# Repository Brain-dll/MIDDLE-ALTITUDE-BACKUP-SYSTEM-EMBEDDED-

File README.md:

# technofest-3000
This project are developed for model rocket competition of technofest. Main purpose is developing avionic systems

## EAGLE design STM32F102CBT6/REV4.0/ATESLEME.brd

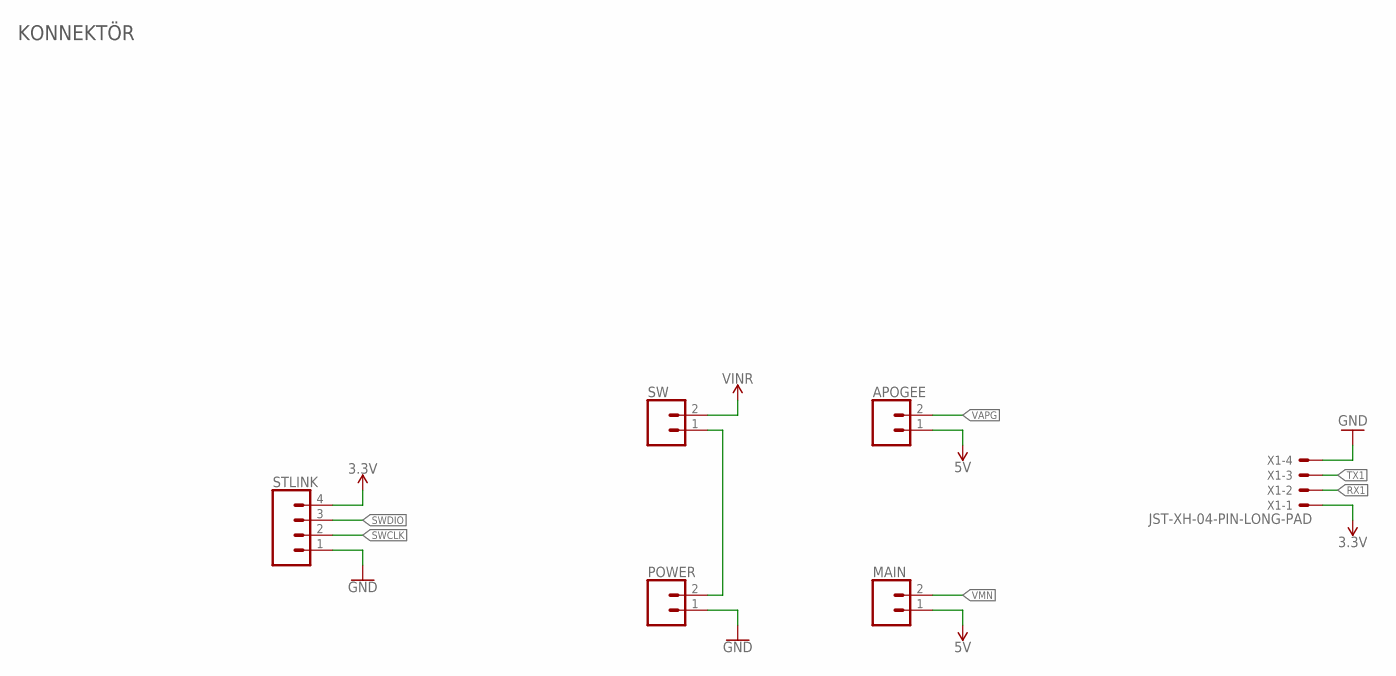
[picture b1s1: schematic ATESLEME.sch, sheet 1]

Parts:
APOGEE: CONN_023.5MM-NO_SILK; SCREWTERMINAL-3.5MM-2-NS
MAIN: CONN_023.5MM-NO_SILK; SCREWTERMINAL-3.5MM-2-NS
POWER: CONN_023.5MM-NO_SILK; SCREWTERMINAL-3.5MM-2-NS
STLINK: CONN_04; 1X04
SW: CONN_023.5MM-NO_SILK; SCREWTERMINAL-3.5MM-2-NS
X1: JST-XH-04-PIN-LONG-PAD; JST-XH-04-PACKAGE-LONG-PAD

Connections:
3.3V: STLINK.4, X1.1; also elsewhere on the board
5V: APOGEE.1, MAIN.1; also elsewhere on the board
GND: POWER.1, STLINK.1, X1.4; also elsewhere on the board
unnamed: POWER.2, SW.1
RX1: X1.2; also elsewhere on the board
SWCLK: STLINK.2; also elsewhere on the board
SWDIO: STLINK.3; also elsewhere on the board
TX1: X1.3; also elsewhere on the board
VAPG: APOGEE.2; also elsewhere on the board
VIN: SW.2; also elsewhere on the board
VMN: MAIN.2; also elsewhere on the board

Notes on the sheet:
KONNEKTÖR

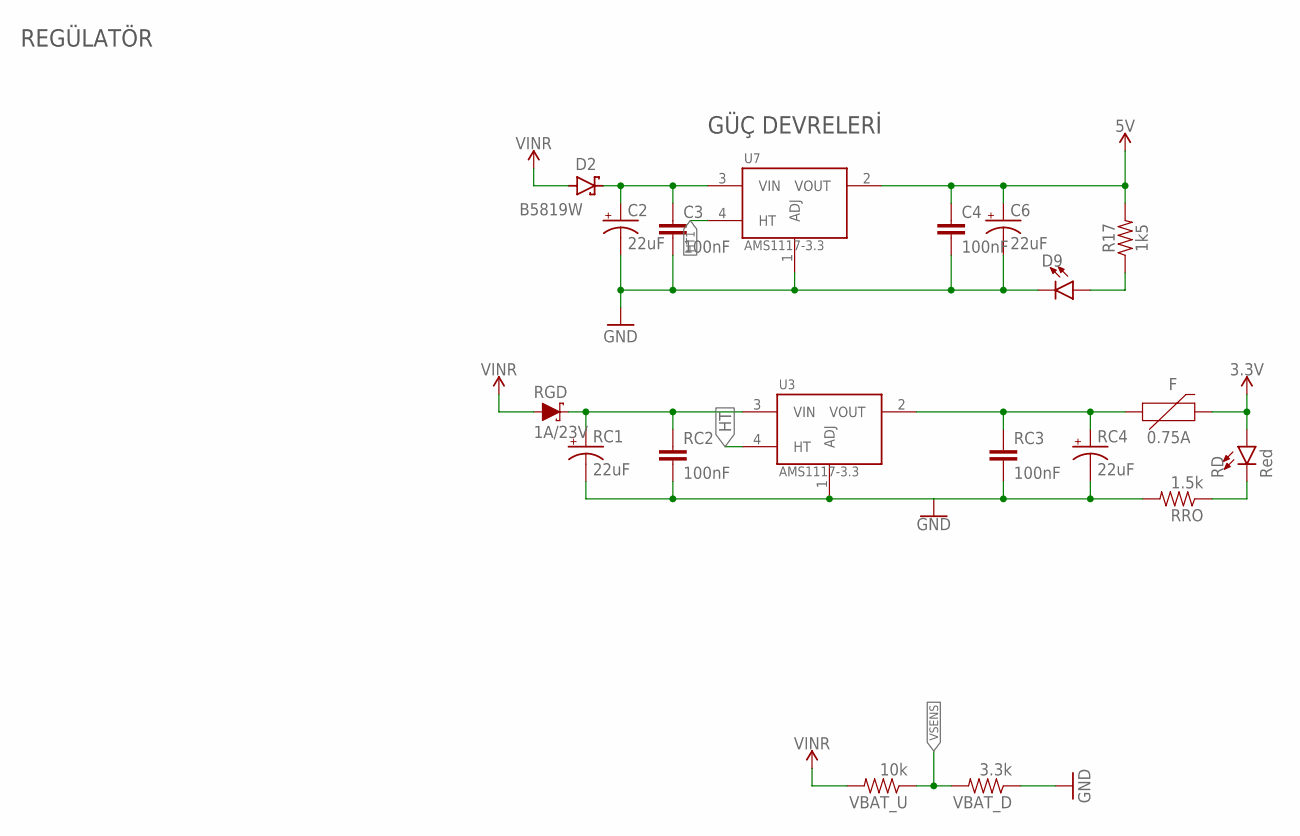
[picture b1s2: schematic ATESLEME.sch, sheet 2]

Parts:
C2, C6: 22uF; EIA3528
C3, C4: 100nF; 0603
D2: B5819W; SODFL3718X115
D9: LED0603; LED-0603
F: 0.75A; 1206
R17: 1k5; 0603
RC1, RC4: 22uF; EIA3528
RC2, RC3: 100nF; 0603
RD: Red; LED-0603
RGD: 1A/23V; SOD-323
RRO: 1.5k; 0603-RES
U3, U7: AMS1117-3.3; SOT229P700X180-4N
VBAT_D: 3.3k; 0603-RES
VBAT_U: 10k; 0603-RES

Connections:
3.3V: F.2, RD.A; also elsewhere on the board
5V: C4.1, C6.A (+), R17.2, U7.2 (VOUT); also elsewhere on the board
GND: C2.C (-), C3.2, C4.2, C6.C (-), D9.C, RC1.C (-), RC2.2, RC3.2, RC4.C (-), RRO.2, U3.1 (ADJ), U7.1 (ADJ), VBAT_D.1; also elsewhere on the board
HT: U3.4 (HT)
HT1: U7.4 (HT)
unnamed: F.1, RC3.1, RC4.A (+), U3.2 (VOUT)
unnamed: RD.C, RRO.1
unnamed: C2.A (+), C3.1, D2.1 (C), U7.3 (VIN)
unnamed: D9.A, R17.1
VIN: D2.2 (A), RGD.A, VBAT_U.2; also elsewhere on the board
VNR: RC1.A (+), RC2.1, RGD.C, U3.3 (VIN)
VSENS: VBAT_D.2, VBAT_U.1; also elsewhere on the board

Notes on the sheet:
REGÜLATÖR
GÜÇ DEVRELERİ

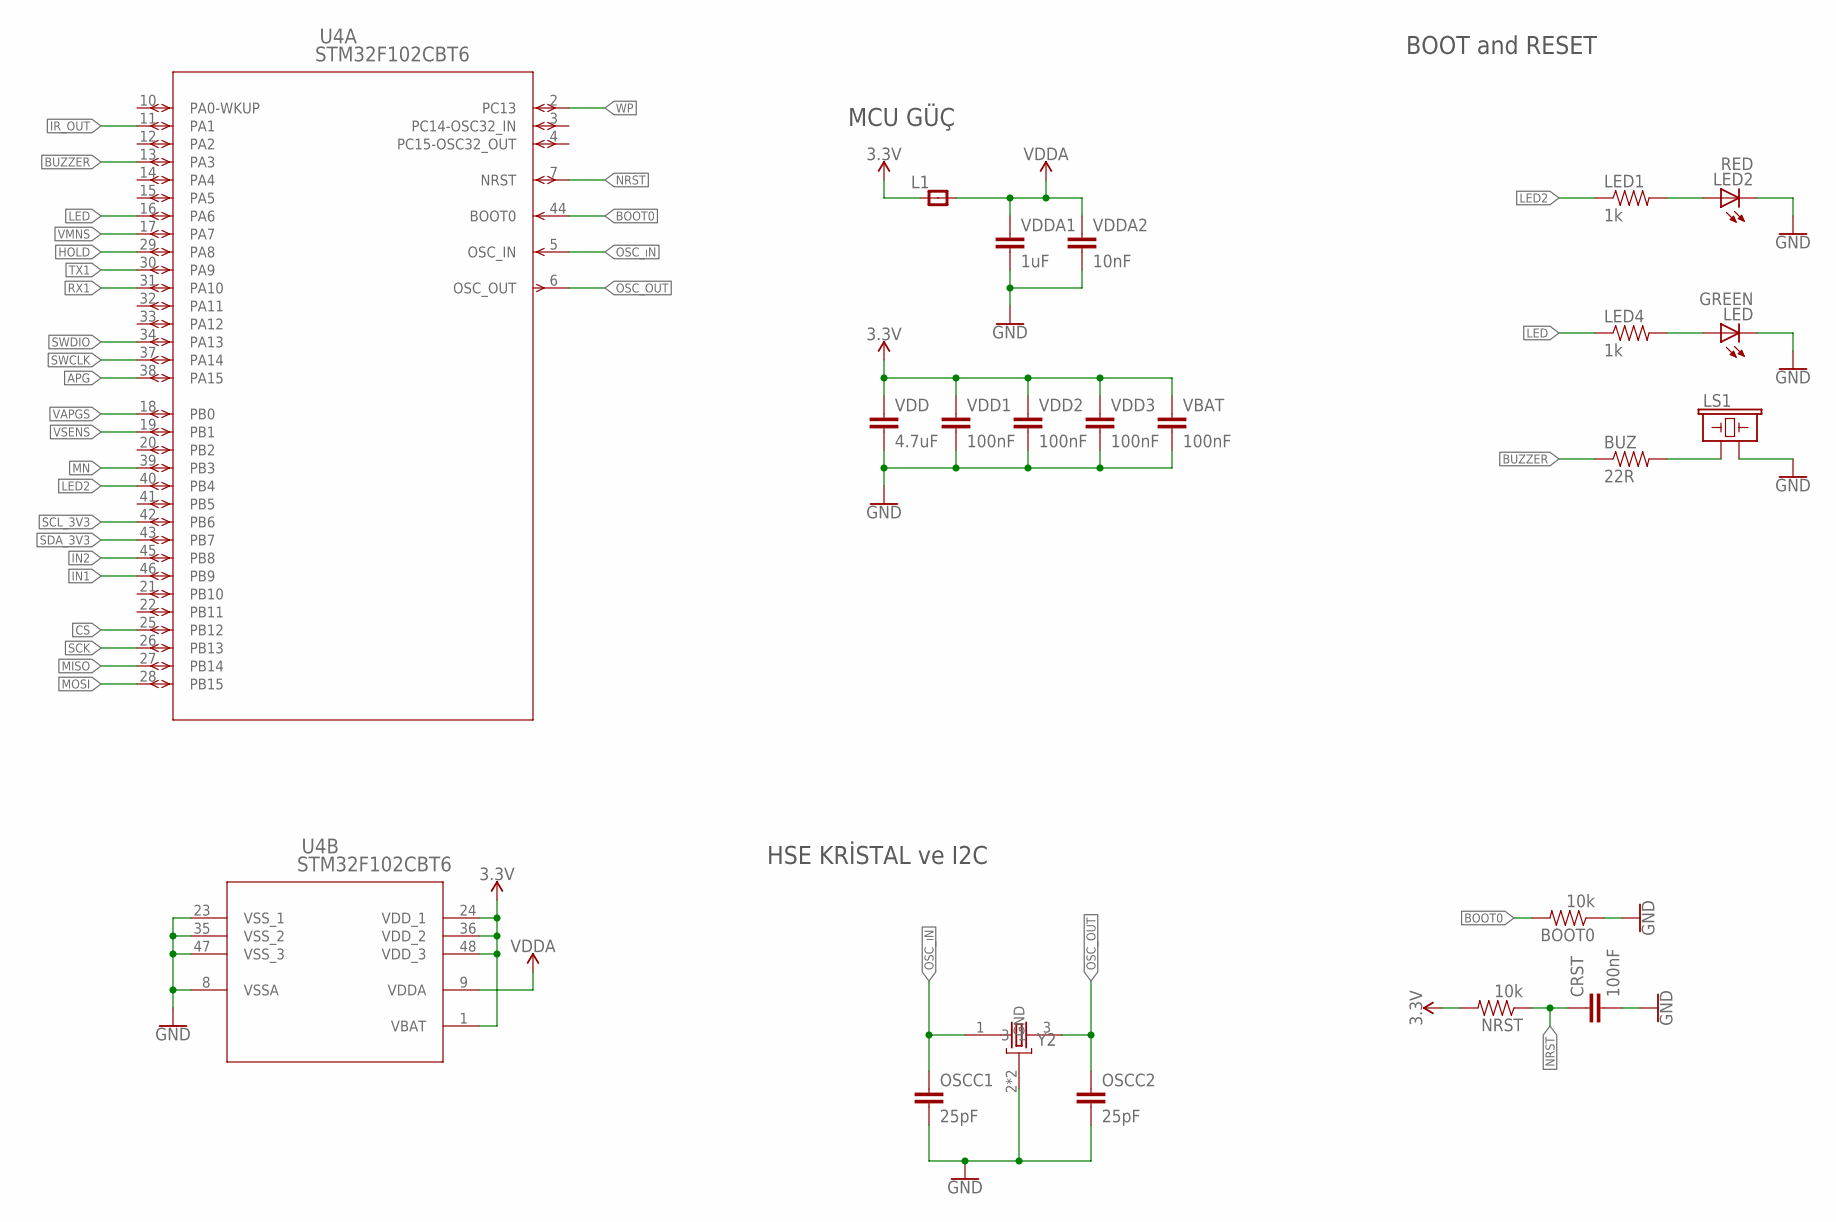
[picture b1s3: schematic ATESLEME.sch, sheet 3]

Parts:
BOOT0: 10k; 0603-RES
BUZ: 22R; 0603-RES
CRST: 100nF; 0603
L1: RC-MASTER-SMD_FB_0805MP; RC-MASTER-SMD_L0805MP
LED: GREEN; LED-0603
LED1, LED4: 1k; 0603-RES
LED2: RED; LED-0603
LS1: BUZZER-PTH; BUZZER-12MM
NRST: 10k; 0603-RES
OSCC1, OSCC2: 25pF; 0603
U4: STM32F102CBT6; LQFP48-7X7MM
VBAT: 100nF; 0603
VDD: 4.7uF; 0603
VDD1, VDD2, VDD3: 100nF; 0603
VDDA1: 1uF; 0603
VDDA2: 10nF; 0603
Y2: ABM2B-8.000MHZ-10-1-U-T; OSCCC500X320X110-4N

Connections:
3.3V: L1.1, NRST.2, U4.1 (VBAT), U4.24 (VDD_1), U4.36 (VDD_2), U4.48 (VDD_3), VBAT.1, VDD.1, VDD1.1, VDD2.1, VDD3.1; also elsewhere on the board
APG: U4.38 (PA15); also elsewhere on the board
BOOT0: BOOT0.2, U4.44 (BOOT0)
BUZZER: BUZ.1, U4.13 (PA3)
CS: U4.25 (PB12); also elsewhere on the board
GND: BOOT0.1, CRST.2, LED.C, LED2.C, LS1.- (2), OSCC1.2, OSCC2.2, U4.8 (VSSA), U4.23 (VSS_1), U4.35 (VSS_2), U4.47 (VSS_3), VBAT.2, VDD.2, VDD1.2, VDD2.2, VDD3.2, VDDA1.2, VDDA2.2, Y2.2 (GND), Y2.4 (GND); also elsewhere on the board
HOLD: U4.29 (PA8); also elsewhere on the board
IN1: U4.46 (PB9); also elsewhere on the board
IN2: U4.45 (PB8); also elsewhere on the board
IR_OUT: U4.11 (PA1); also elsewhere on the board
LED: LED4.1, U4.16 (PA6)
LED2: LED1.1, U4.40 (PB4)
MISO: U4.27 (PB14); also elsewhere on the board
MN: U4.39 (PB3); also elsewhere on the board
MOSI: U4.28 (PB15); also elsewhere on the board
unnamed: LED1.2, LED2.A
unnamed: LED.A, LED4.2
unnamed: BUZ.2, LS1.+ (1)
NRST: CRST.1, NRST.1, U4.7 (NRST)
OSC_OUT: OSCC2.1, U4.6 (OSC_OUT), Y2.3
OSC_ıN: OSCC1.1, U4.5 (OSC_IN), Y2.1
RX1: U4.31 (PA10); also elsewhere on the board
SCK: U4.26 (PB13); also elsewhere on the board
SCL_3V3: U4.42 (PB6); also elsewhere on the board
SDA_3V3: U4.43 (PB7); also elsewhere on the board
SWCLK: U4.37 (PA14); also elsewhere on the board
SWDIO: U4.34 (PA13); also elsewhere on the board
TX1: U4.30 (PA9); also elsewhere on the board
VAPGS: U4.18 (PB0); also elsewhere on the board
VDDA: L1.2, U4.9 (VDDA), VDDA1.1, VDDA2.1
VMNS: U4.17 (PA7); also elsewhere on the board
VSENS: U4.19 (PB1); also elsewhere on the board
WP: U4.2 (PC13); also elsewhere on the board

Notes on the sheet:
HSE KRİSTAL ve I2C
MCU GÜÇ
BOOT and RESET

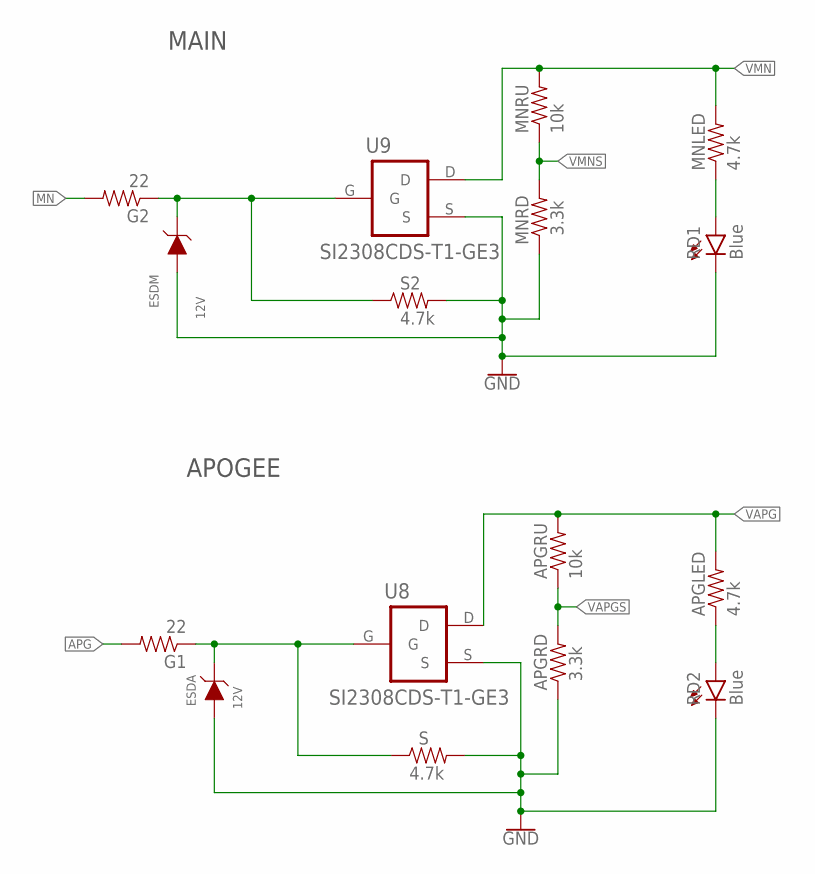
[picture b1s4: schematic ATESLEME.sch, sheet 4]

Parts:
APGLED: 4.7k; 0603-RES
APGRD: 3.3k; 0603-RES
APGRU: 10k; 0603-RES
ESDA: 12V; WE-TVSP_DO-214AC_UNIDIRECTIONAL
ESDM: 12V; WE-TVSP_DO-214AC_UNIDIRECTIONAL
G1, G2: 22; 0603-RES
MNLED: 4.7k; 0603-RES
MNRD: 3.3k; 0603-RES
MNRU: 10k; 0603-RES
RD1, RD2: Blue; LED-0603
S, S2: 4.7k; 0603-RES
U8, U9: SI2308CDS-T1-GE3; SOT95P240X112-3N

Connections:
APG: G1.2; also elsewhere on the board
GND: APGRD.1, ESDA.2 (A), ESDM.2 (A), MNRD.1, RD1.C, RD2.C, S.2, S2.2, U8.S, U9.S; also elsewhere on the board
MN: G2.2; also elsewhere on the board
unnamed: MNLED.1, RD1.A
unnamed: APGLED.1, RD2.A
unnamed: ESDM.1 (C), G2.1, S2.1, U9.G
unnamed: ESDA.1 (C), G1.1, S.1, U8.G
VAPG: APGLED.2, APGRU.2, U8.D; also elsewhere on the board
VAPGS: APGRD.2, APGRU.1; also elsewhere on the board
VMN: MNLED.2, MNRU.2, U9.D; also elsewhere on the board
VMNS: MNRD.2, MNRU.1; also elsewhere on the board

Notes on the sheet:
MAIN
APOGEE

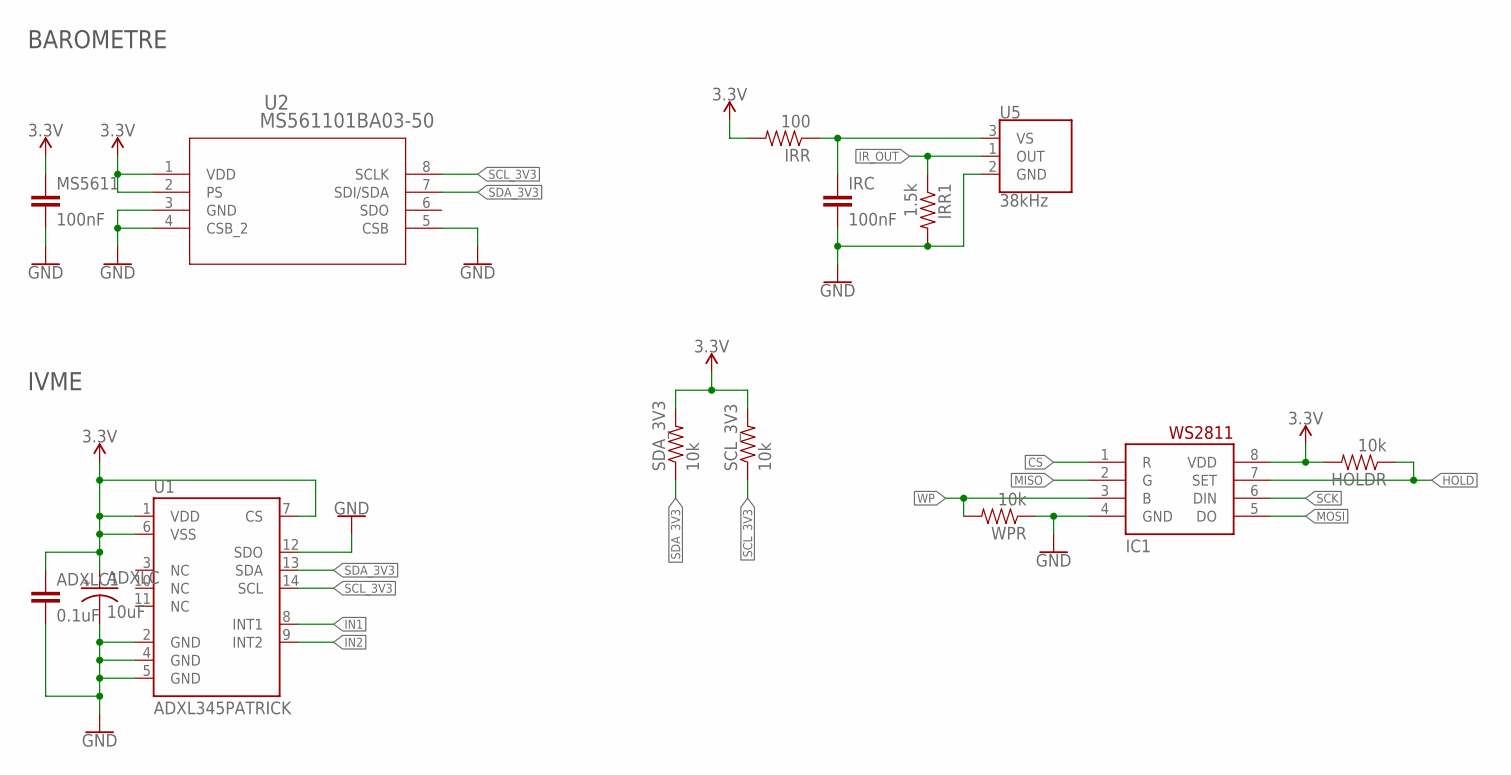
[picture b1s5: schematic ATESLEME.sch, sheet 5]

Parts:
ADXLC: 10uF; EIA3216
ADXLC1: 0.1uF; 0603
HOLDR: 10k; 0603-RES
IC1: EN25F40-100GCP-TR; SO08-SKINNYPADS
IRC: 100nF; 0603
IRR: 100; 0603-RES
IRR1: 1.5k; 0603-RES
MS5611: 100nF; 0603
SCL_3V3: 10k; 0603-RES
SDA_3V3: 10k; 0603-RES
U1: ADXL345PATRICK; LGA14_1:1_PATRICK
U2: MS561101BA03-50; SON8_MS5611_TEC
U5: 38kHz; TSOP382
WPR: 10k; 0603-RES

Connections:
3.3V: ADXLC.+, ADXLC1.1, HOLDR.2, IC1.8 (VDD), IRR.2, MS5611.1, SCL_3V3.2, SDA_3V3.2, U1.1 (VDD), U1.6 (VSS), U1.7 (CS), U2.1 (VDD), U2.2 (PS); also elsewhere on the board
CS: IC1.1 (R); also elsewhere on the board
GND: ADXLC.-, ADXLC1.2, IC1.4 (GND), IRC.2, IRR1.2, MS5611.2, U1.2 (GND), U1.4 (GND), U1.5 (GND), U1.12 (SDO), U2.3 (GND), U2.4 (CSB_2), U2.5 (CSB), U5.2 (GND), WPR.1; also elsewhere on the board
HOLD: HOLDR.1, IC1.7 (SET); also elsewhere on the board
IN1: U1.8 (INT1); also elsewhere on the board
IN2: U1.9 (INT2); also elsewhere on the board
IR_OUT: IRR1.1, U5.1 (OUT); also elsewhere on the board
MISO: IC1.2 (G); also elsewhere on the board
MOSI: IC1.5 (DO); also elsewhere on the board
unnamed: IRC.1, IRR.1, U5.3 (VS)
SCK: IC1.6 (DIN); also elsewhere on the board
SCL_3V3: SCL_3V3.1, U1.14 (SCL), U2.8 (SCLK); also elsewhere on the board
SDA_3V3: SDA_3V3.1, U1.13 (SDA), U2.7 (SDI/SDA); also elsewhere on the board
WP: IC1.3 (B), WPR.2; also elsewhere on the board

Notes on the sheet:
BAROMETRE
IVME

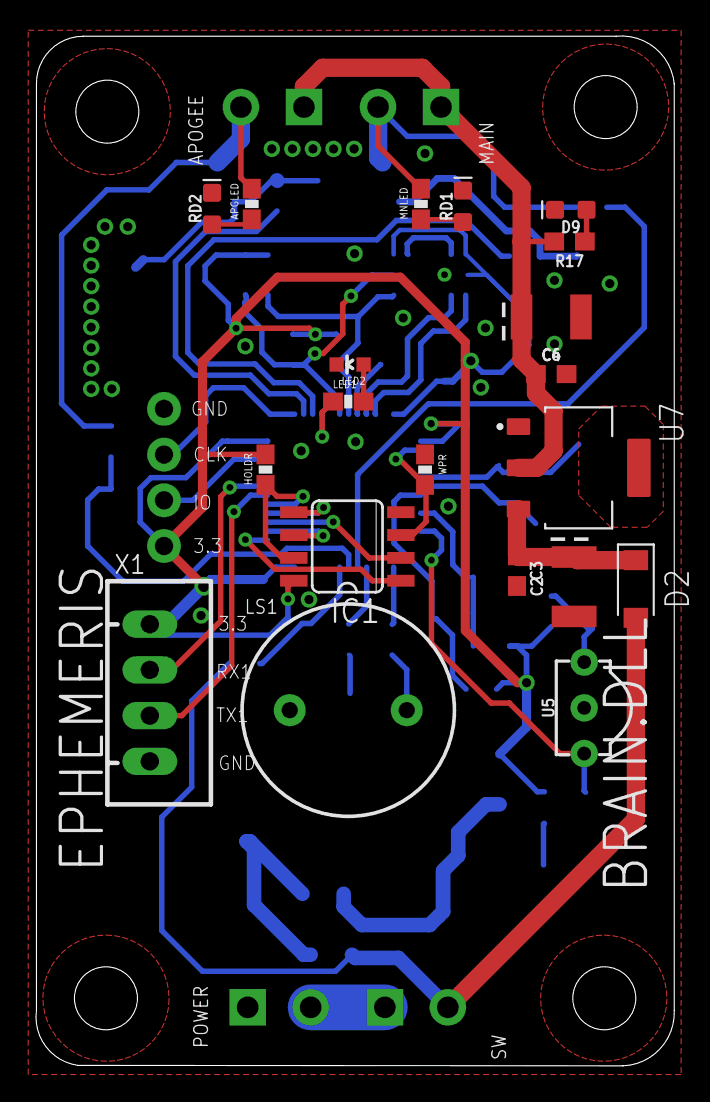
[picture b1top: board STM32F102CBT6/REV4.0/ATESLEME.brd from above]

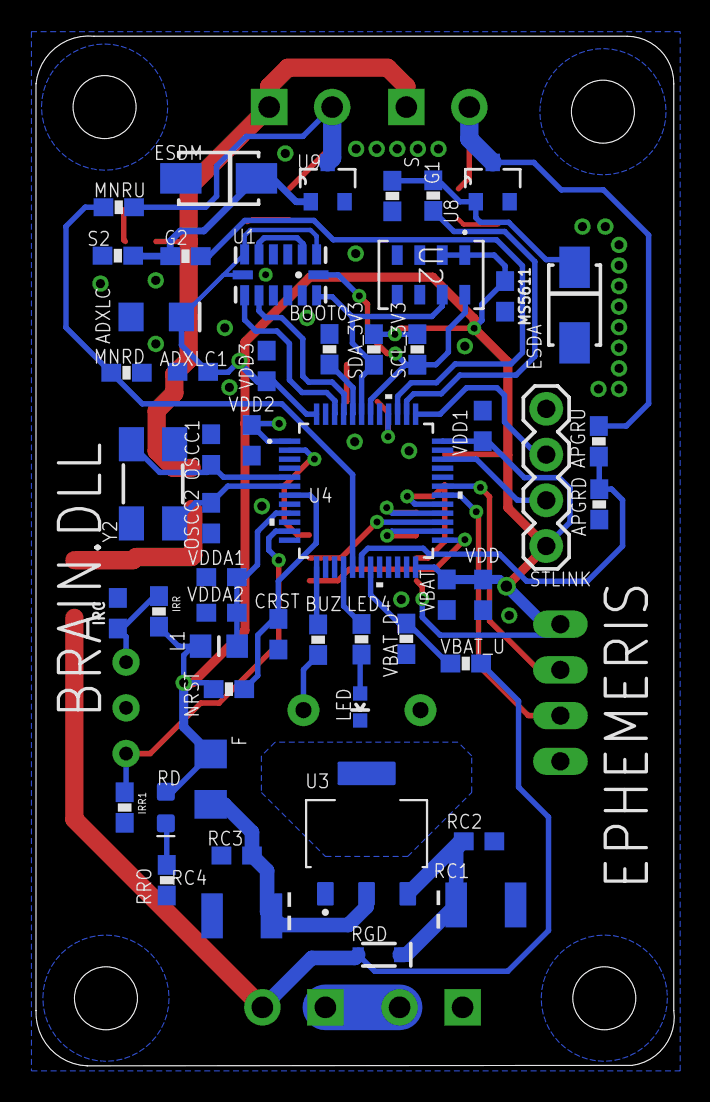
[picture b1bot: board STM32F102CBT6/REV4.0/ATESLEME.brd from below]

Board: 2 copper layers, 35.5 x 57.2 mm, 76 parts (52 on the bottom side), 48 nets.

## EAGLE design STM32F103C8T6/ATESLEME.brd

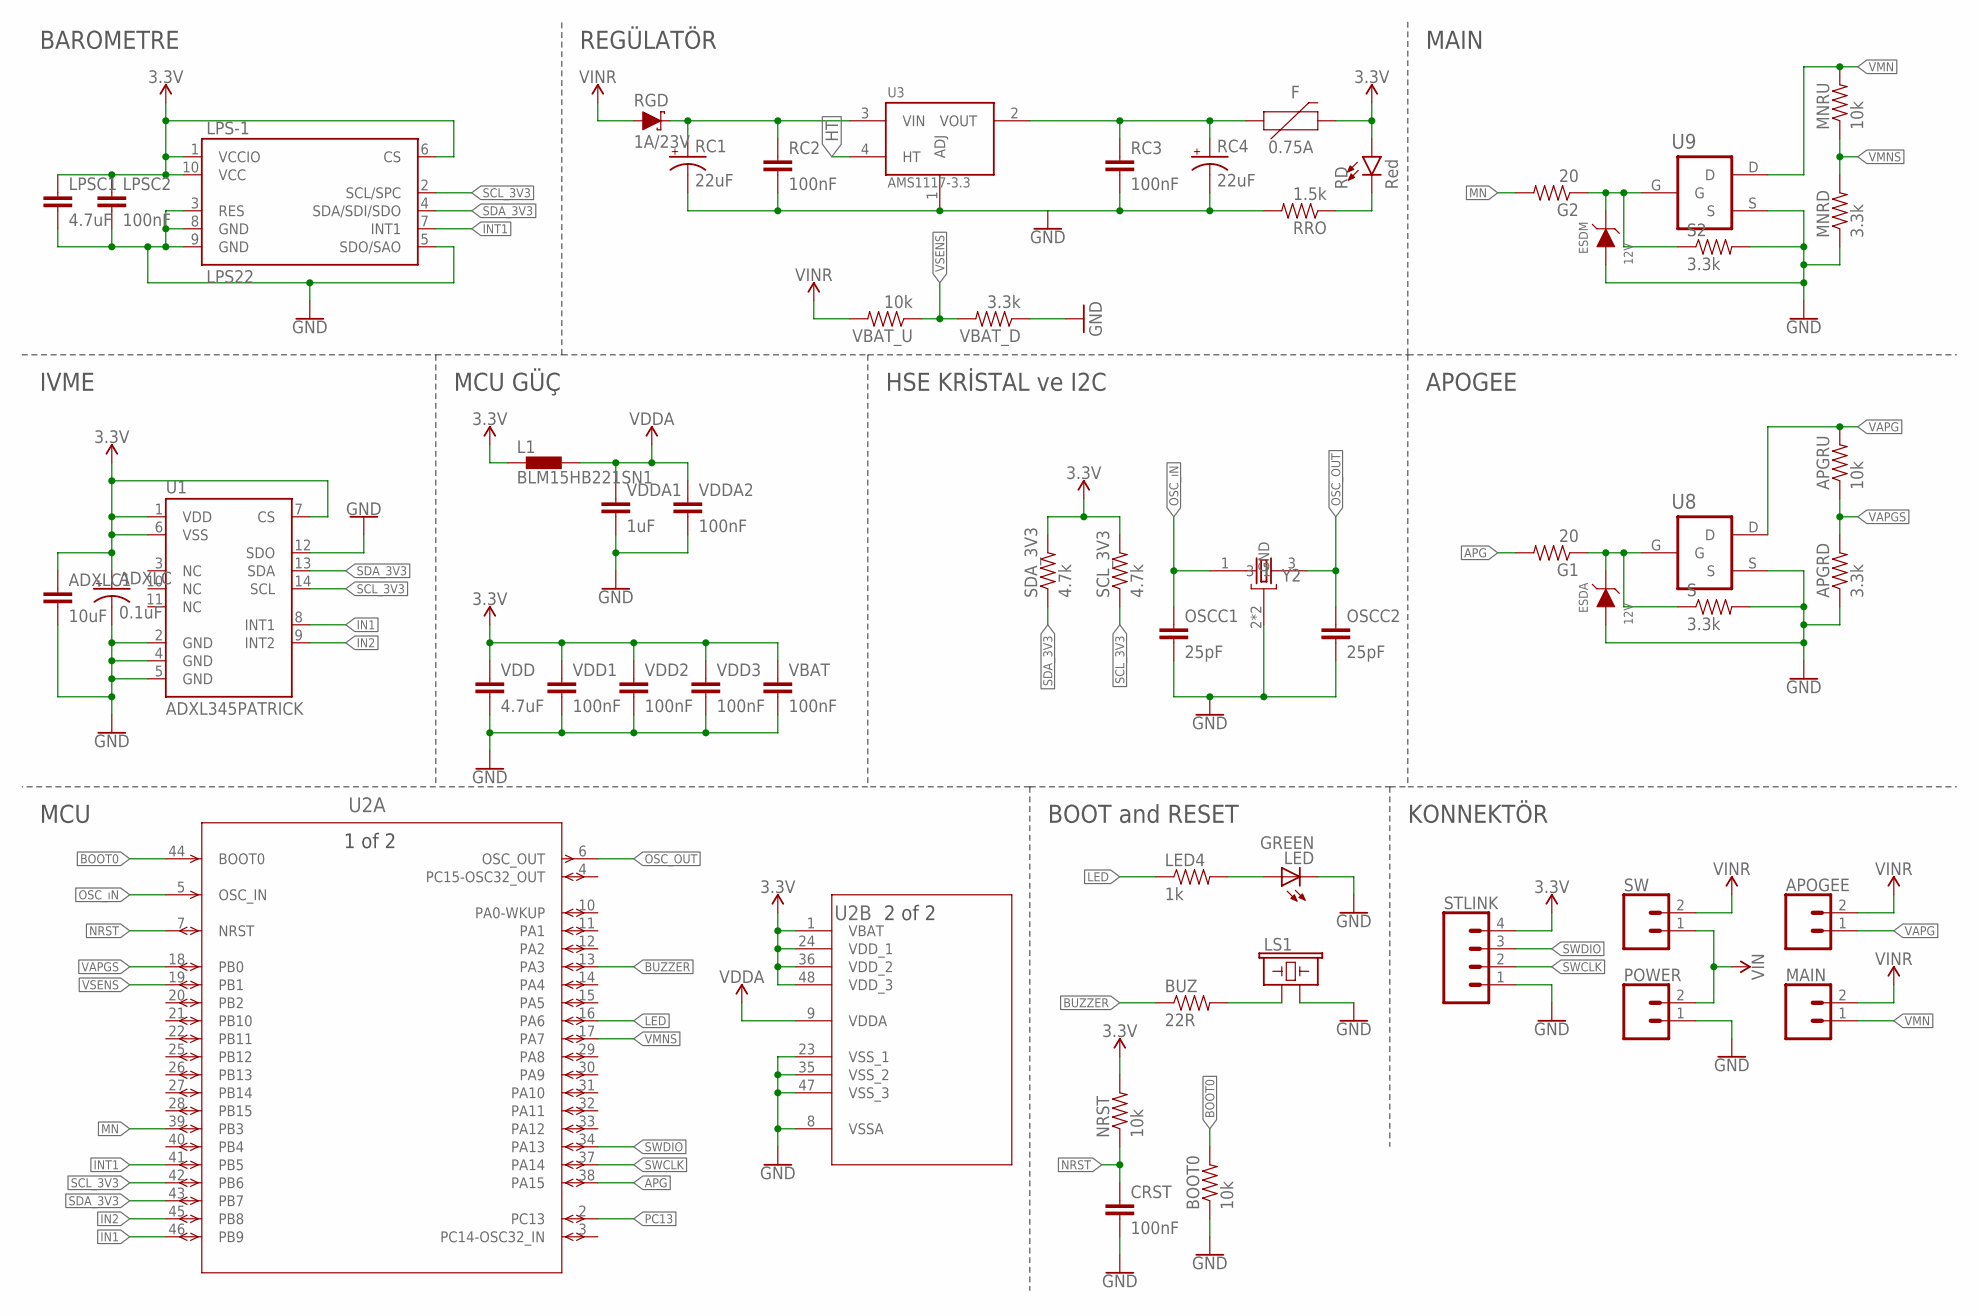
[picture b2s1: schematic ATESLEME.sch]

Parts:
ADXLC: 0.1uF; EIA3216
ADXLC1: 10uF; 0603
APGRD: 3.3k; 0603-RES
APGRU: 10k; 0603-RES
APOGEE: CONN_023.5MM-NO_SILK; SCREWTERMINAL-3.5MM-2-NS
BOOT0: 10k; 0603-RES
BUZ: 22R; 0603-RES
CRST: 100nF; 0603
ESDA: 12V; WE-TVSP_DO-214AC_UNIDIRECTIONAL
ESDM: 12V; WE-TVSP_DO-214AC_UNIDIRECTIONAL
F: 0.75A; 1206
G1, G2: 20; 0603-RES
L1: BLM15HB221SN1; 0402
LED: GREEN; LED-0603
LED4: 1k; 0603-RES
LPS-1: LPS22; LPS22H
LPSC1: 4.7uF; 0603
LPSC2: 100nF; 0603
LS1: BUZZER-PTH; BUZZER-12MM
MAIN: CONN_023.5MM-NO_SILK; SCREWTERMINAL-3.5MM-2-NS
MNRD: 3.3k; 0603-RES
MNRU: 10k; 0603-RES
NRST: 10k; 0603-RES
OSCC1, OSCC2: 25pF; 0603
POWER: CONN_023.5MM-NO_SILK; SCREWTERMINAL-3.5MM-2-NS
RC1, RC4: 22uF; EIA3528
RC2, RC3: 100nF; 0603
RD: Red; LED-0603
RGD: 1A/23V; SOD-323
RRO: 1.5k; 0603-RES
S, S2: 3.3k; 0603-RES
SCL_3V3: 4.7k; 0603-RES
SDA_3V3: 4.7k; 0603-RES
STLINK: CONN_04; 1X04
SW: CONN_023.5MM-NO_SILK; SCREWTERMINAL-3.5MM-2-NS
U1: ADXL345PATRICK; LGA14_1:1_PATRICK
U2: STM32F103C8T6; LQFP48-7X7MM
U3: AMS1117-3.3; SOT229P700X180-4N
U8, U9: IRLML6344TRPBF; SOT95P240X112-3N
VBAT: 100nF; 0603
VBAT_D: 3.3k; 0603-RES
VBAT_U: 10k; 0603-RES
VDD: 4.7uF; 0603
VDD1, VDD2, VDD3: 100nF; 0603
VDDA1: 1uF; 0603
VDDA2: 100nF; 0603
Y2: ABM2B-8.000MHZ-10-1-U-T; OSCCC500X320X110-4N

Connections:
3.3V: ADXLC.+, ADXLC1.1, F.2, L1.1, LPS-1.1 (VCCIO), LPS-1.6 (CS), LPS-1.10 (VCC), LPSC1.1, LPSC2.1, NRST.2, RD.A, SCL_3V3.2, SDA_3V3.2, STLINK.4, U1.1 (VDD), U1.6 (VSS), U1.7 (CS), U2.1 (VBAT), U2.24 (VDD_1), U2.36 (VDD_2), U2.48 (VDD_3), VBAT.1, VDD.1, VDD1.1, VDD2.1, VDD3.1
APG: G1.2, U2.38 (PA15)
BOOT0: BOOT0.2, U2.44 (BOOT0)
BUZZER: BUZ.1, U2.13 (PA3)
GND: ADXLC.-, ADXLC1.2, APGRD.1, BOOT0.1, CRST.2, ESDA.2 (A), ESDM.2 (A), LED.C, LPS-1.3 (RES), LPS-1.5 (SDO/SAO), LPS-1.8 (GND), LPS-1.9 (GND), LPSC1.2, LPSC2.2, LS1.- (2), MNRD.1, OSCC1.2, OSCC2.2, POWER.1, RC1.C (-), RC2.2, RC3.2, RC4.C (-), RRO.2, S.2, S2.2, STLINK.1, U1.2 (GND), U1.4 (GND), U1.5 (GND), U1.12 (SDO), U2.8 (VSSA), U2.23 (VSS_1), U2.35 (VSS_2), U2.47 (VSS_3), U3.1 (ADJ), U8.S, U9.S, VBAT.2, VBAT_D.1, VDD.2, VDD1.2, VDD2.2, VDD3.2, VDDA1.2, VDDA2.2, Y2.2 (GND), Y2.4 (GND)
HT: U3.4 (HT)
IN1: U1.8 (INT1), U2.46 (PB9)
IN2: U1.9 (INT2), U2.45 (PB8)
INT1: LPS-1.7 (INT1), U2.41 (PB5)
LED: LED4.1, U2.16 (PA6)
MN: G2.2, U2.39 (PB3)
unnamed: F.1, RC3.1, RC4.A (+), U3.2 (VOUT)
unnamed: RD.C, RRO.1
unnamed: ESDM.1 (C), G2.1, S2.1, U9.G
unnamed: LED.A, LED4.2
unnamed: BUZ.2, LS1.+ (1)
unnamed: ESDA.1 (C), G1.1, S.1, U8.G
NRST: CRST.1, NRST.1, U2.7 (NRST)
OSC_OUT: OSCC2.1, U2.6 (OSC_OUT), Y2.3
OSC_ıN: OSCC1.1, U2.5 (OSC_IN), Y2.1
PC13: U2.2 (PC13)
SCL_3V3: LPS-1.2 (SCL/SPC), SCL_3V3.1, U1.14 (SCL), U2.42 (PB6)
SDA_3V3: LPS-1.4 (SDA/SDI/SDO), SDA_3V3.1, U1.13 (SDA), U2.43 (PB7)
SWCLK: STLINK.2, U2.37 (PA14)
SWDIO: STLINK.3, U2.34 (PA13)
VAPG: APGRU.2, APOGEE.1, U8.D
VAPGS: APGRD.2, APGRU.1, U2.18 (PB0)
VCC: POWER.2, SW.1
VDDA: L1.2, U2.9 (VDDA), VDDA1.1, VDDA2.1
VIN: APOGEE.2, MAIN.2, RGD.A, SW.2, VBAT_U.2
VMN: MAIN.1, MNRU.2, U9.D
VMNS: MNRD.2, MNRU.1, U2.17 (PA7)
VNR: RC1.A (+), RC2.1, RGD.C, U3.3 (VIN)
VSENS: U2.19 (PB1), VBAT_D.2, VBAT_U.1

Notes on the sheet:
BAROMETRE
KONNEKTÖR
IVME
HSE KRİSTAL ve I2C
MCU
REGÜLATÖR
MAIN
MCU GÜÇ
BOOT and RESET
APOGEE

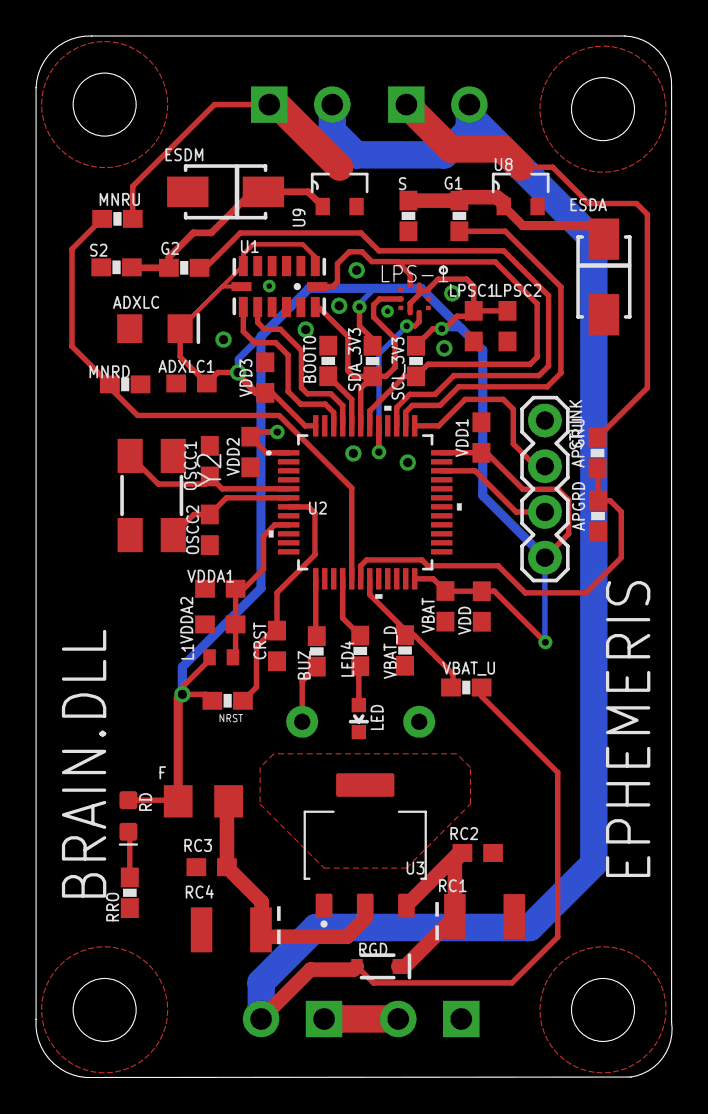
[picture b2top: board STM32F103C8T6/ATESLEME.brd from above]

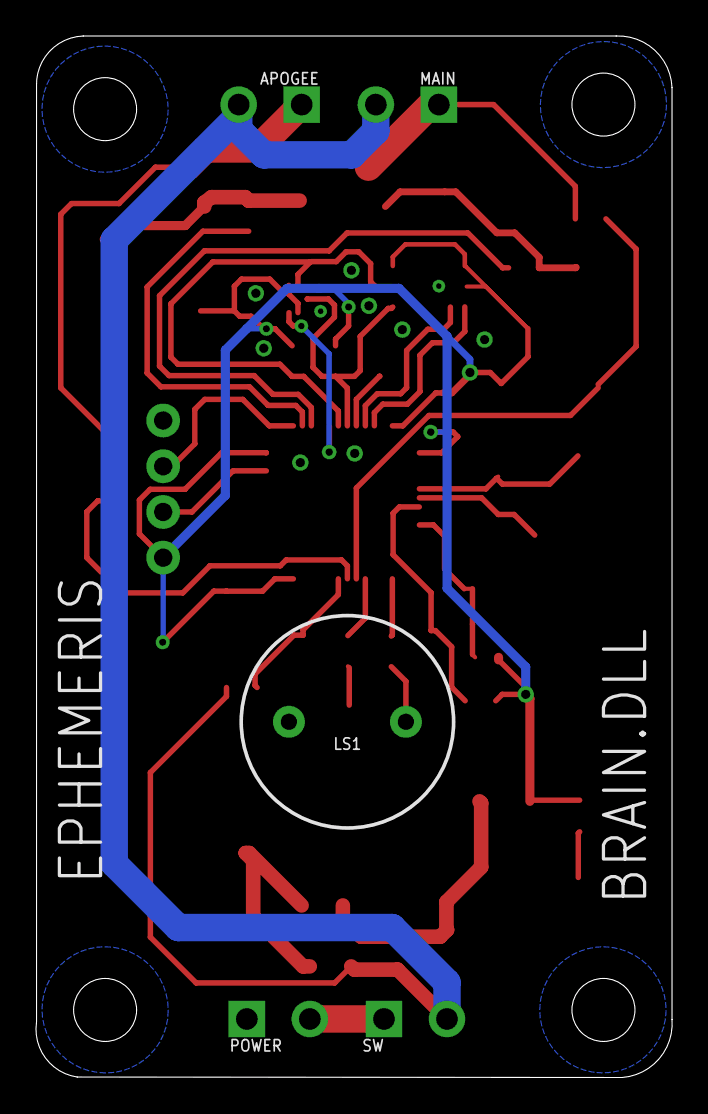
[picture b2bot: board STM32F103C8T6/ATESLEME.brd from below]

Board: 2 copper layers, 35.3 x 57.9 mm, 55 parts (5 on the bottom side), 32 nets.

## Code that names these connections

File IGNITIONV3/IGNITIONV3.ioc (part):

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Mcu.Name=STM32F102C(8-B)Tx
Mcu.Package=LQFP48
Mcu.UserName=STM32F102CBTx
PA13.Mode=Serial_Wire
PA13.Signal=SYS_JTMS-SWDIO
PA14.Mode=Serial_Wire
PA14.Signal=SYS_JTCK-SWCLK
PA15.GPIOParameters=GPIO_Label
PA15.GPIO_Label=APOGEE
PA15.Signal=GPIO_Output
PA3.GPIOParameters=GPIO_Label
PA3.GPIO_Label=BUZZER
PA3.Signal=GPIO_Output
PA6.GPIOParameters=GPIO_Label
PA6.GPIO_Label=BOTTOM_LED
PA6.Signal=GPIO_Output
PB1.GPIOParameters=GPIO_Label
PB1.GPIO_Label=VSENS
PB1.Signal=ADCx_IN9
PB3.GPIOParameters=GPIO_Label
PB3.GPIO_Label=MAIN
PB3.Signal=GPIO_Output
PB4.GPIOParameters=GPIO_Label
PB4.GPIO_Label=TOP_LED
PB4.Signal=GPIO_Output
PB6.Mode=I2C
PB6.Signal=I2C1_SCL
PB7.Mode=I2C
PB7.Signal=I2C1_SDA
PD0-OSC_IN.Mode=HSE-External-Oscillator
PD0-OSC_IN.Signal=RCC_OSC_IN
PD1-OSC_OUT.Mode=HSE-External-Oscillator
PD1-OSC_OUT.Signal=RCC_OSC_OUT
RCC.SYSCLKFreq_VALUE=48000000
RCC.SYSCLKSource=RCC_SYSCLKSOURCE_PLLCLK
board=custom

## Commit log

2021-02-27 Ignition computer was comleted and cad file was builed
2021-02-28 Guard ring was located around of HSE crystal
2021-02-28 Documents of ignition computer was uploaded
2021-03-03 Discrite polygon was applied to heat pad of AMS1117-3.3
2021-03-05 Some vias was putted near the sources of NMOS's
2021-03-06 Drill size maken 20 diameter
2021-03-08 Telemetry V1.0.0 was completed
2021-03-08 Telemetry system was moved to new repository
2021-03-08 some modification was maken on the routes
2021-03-10 Routes are be extended
2021-03-10 LOGO was uploaded
2021-03-14 Extra polygon was added for methal distance
2021-03-24 Redesign was maken for ignition
2021-03-26 New version of boards with new controller was designed
2021-03-28 Preparing for first order
2021-04-03 Polygon witdh was increased IMPORTANT
2021-04-03 Polygon 15 mils
2021-04-06 NMOS trace was be expanded and 1206 package version was created
2021-04-08 packages was modified according to stock situation
2021-04-19 Some modification was done
2021-05-03 Component name locations was arranged
2021-05-29 Revision V2.0.0 was released
2021-06-02 Version 2.0 was updated by brain.dll
2021-06-30 VDDA cap calue was changed
2021-07-05 Regulator was added for e match and released new two version for ordering
2021-08-08 Sotware and Algorithm was added
2021-08-15 Sofware was updated
2021-08-31 Last updates was completed, Ready for flying
2021-09-17 Software and Hardware are stable
2021-09-17 Unneccessary file was deleted

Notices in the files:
parts and their libraries:
SparkFun-PowerSymbols: Licensing: Creative Commons ShareAlike 4.0 International - https://creativecommons.org/licenses/by-sa/4.0
Arduino-Sensors: Copyright (c) 2016-2017 Arduino LLC.  All right reserved.
Wurth_EMC Components_WE-TVSP: Copyright: Würth Elektronik
